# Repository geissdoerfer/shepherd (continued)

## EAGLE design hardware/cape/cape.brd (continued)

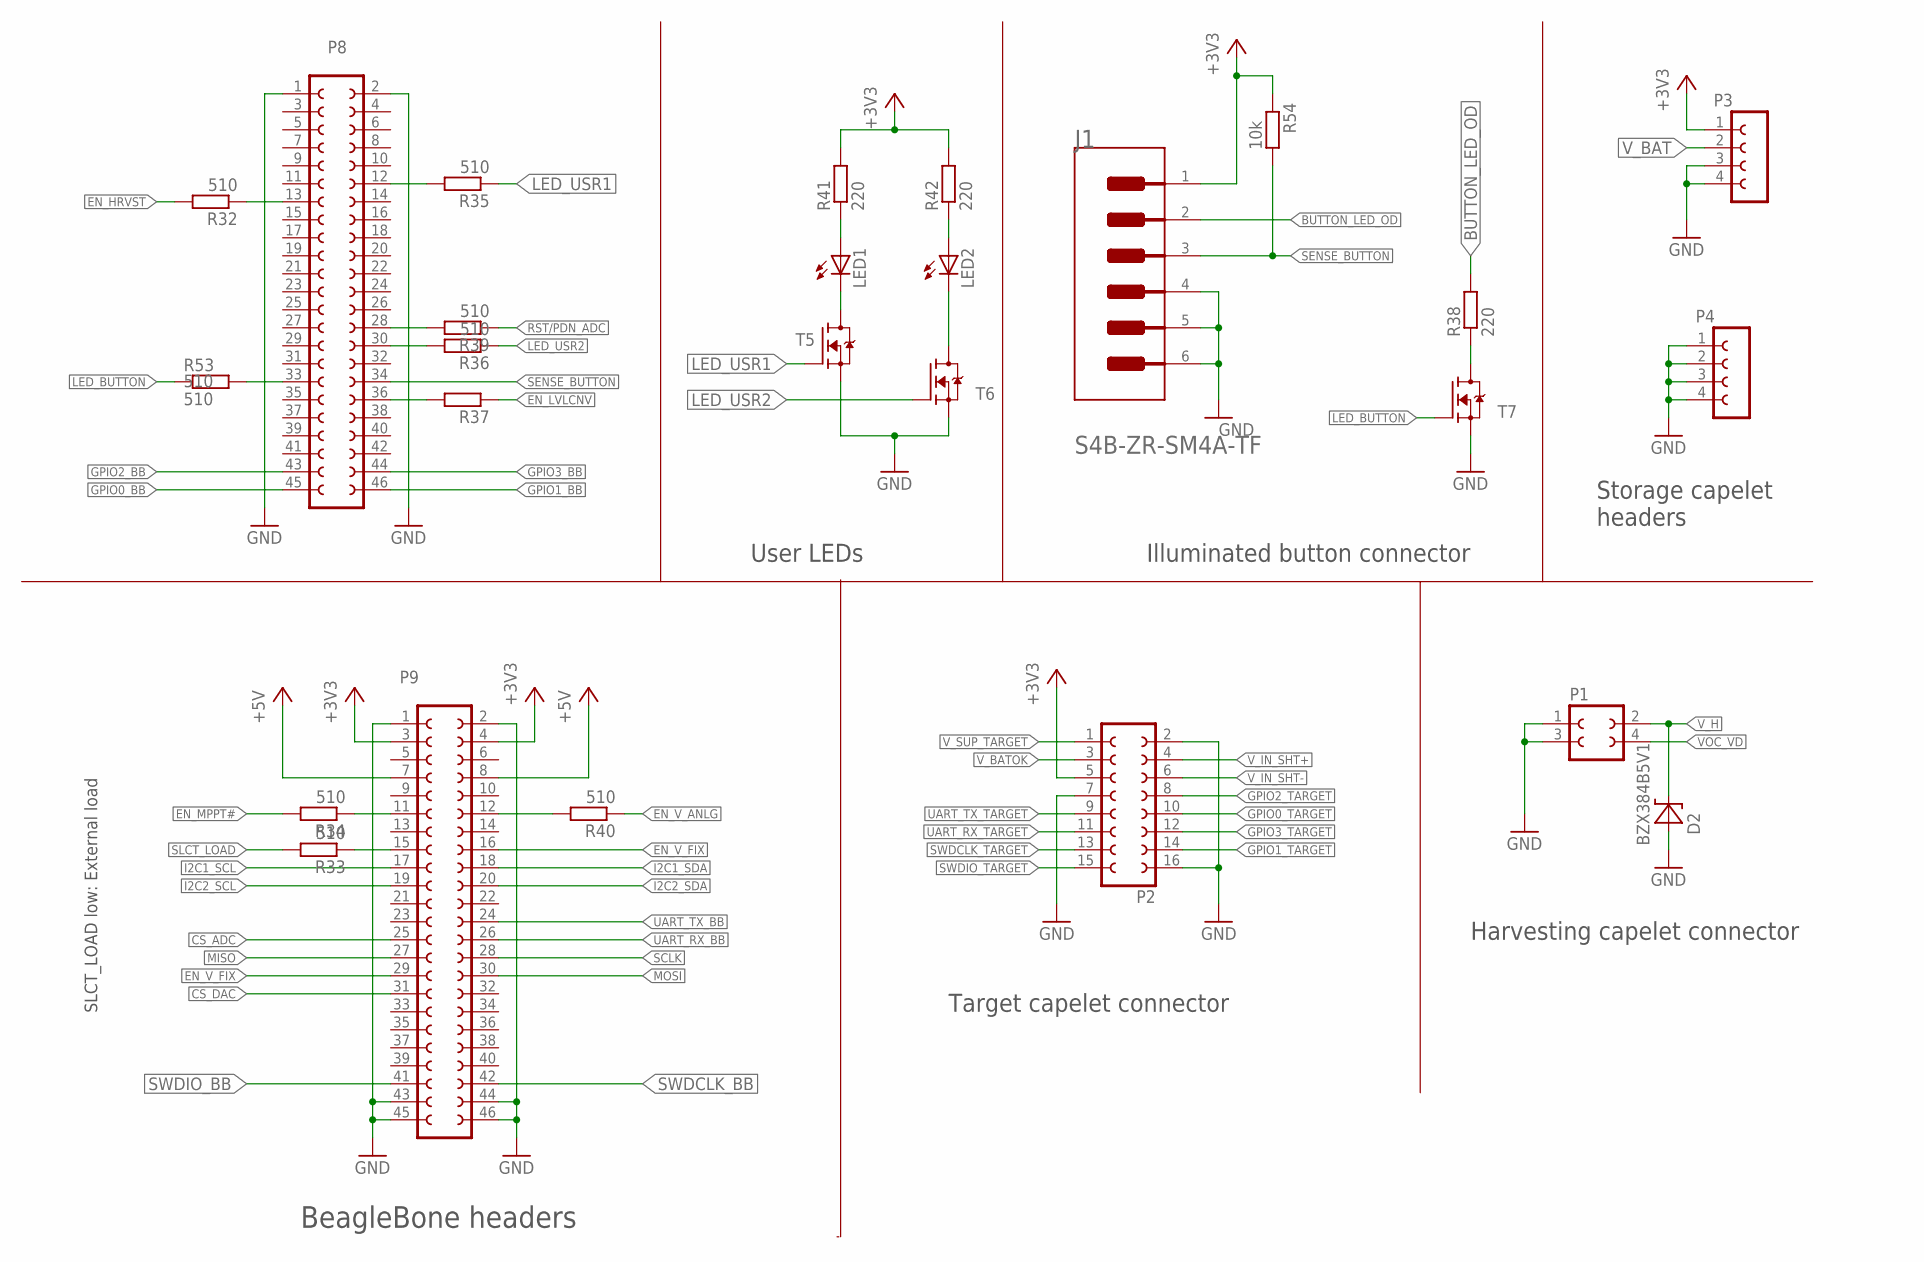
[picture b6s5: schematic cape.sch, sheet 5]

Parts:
D2: BZX384B5V1; SOD2513X110
J1: JST_S4B-ZR-SM4A-TFJST_S4B-ZR-SM4A-TF_0_0; JST_S4B-ZR-SM4A-TF_0
LED1, LED2: 598-8130-107FLED_0805; LEDC2012X75
P1: FE02-2
P2: FE08-2
P3, P4: FE04-1
P8, P9: FE23-2
R32, R33, R34, R35, R36, R37, R39, R40, R53: 510; RESC1005X40
R38, R41, R42: 220; RESC1608X55
R54: 10k; RESC1005X40
T5, T6, T7: SI2374DSSOT23-VSHAY; SOT95P237X112-3

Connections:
+3V3: J1.1, P2.5, P3.1, P9.3, P9.4, R41.2, R42.2, R54.1; also elsewhere on the board
+5V: P9.7, P9.8; also elsewhere on the board
BUTTON_LED_OD: J1.2, R38.2
CS_ADC: P9.25; also elsewhere on the board
CS_DAC: P9.31; also elsewhere on the board
EN_HRVST: R32.2; also elsewhere on the board
EN_LVLCNV: R37.1; also elsewhere on the board
EN_MPPT#: R34.2; also elsewhere on the board
EN_V_ANLG: R40.1; also elsewhere on the board
EN_V_FIX: P9.16, P9.29; also elsewhere on the board
GND: D2.2 (A), J1.4, J1.5 (MNT_1), J1.6 (MNT_2), P1.1, P1.3, P2.2, P2.7, P2.16, P3.3, P3.4, P4.1, P4.2, P4.3, P4.4, P8.1, P8.2, P9.1, P9.2, P9.43, P9.44, P9.45, P9.46, T5.2 (S), T6.2 (S), T7.2 (S); also elsewhere on the board
GPIO0_BB: P8.45; also elsewhere on the board
GPIO0_TARGET: P2.10; also elsewhere on the board
GPIO1_BB: P8.46; also elsewhere on the board
GPIO1_TARGET: P2.14; also elsewhere on the board
GPIO2_BB: P8.43; also elsewhere on the board
GPIO2_TARGET: P2.8; also elsewhere on the board
GPIO3_BB: P8.44; also elsewhere on the board
GPIO3_TARGET: P2.12; also elsewhere on the board
I2C1_SCL: P9.17; also elsewhere on the board
I2C1_SDA: P9.18; also elsewhere on the board
I2C2_SCL: P9.19; also elsewhere on the board
I2C2_SDA: P9.20; also elsewhere on the board
LED_BUTTON: R53.1, T7.1 (G)
LED_USR1: R35.1, T5.1 (G)
LED_USR2: R36.1, T6.1 (G)
MISO: P9.27; also elsewhere on the board
MOSI: P9.30; also elsewhere on the board
unnamed: LED1.1 (C), T5.3 (D)
unnamed: P8.13, R32.1
unnamed: P9.15, R33.1
unnamed: P8.28, R39.2
unnamed: P8.33, R53.2
unnamed: P8.36, R37.2
unnamed: LED1.2 (A), R41.1
unnamed: P8.12, R35.2
unnamed: LED2.1 (C), T6.3 (D)
unnamed: LED2.2 (A), R42.1
unnamed: P9.11, R34.1
unnamed: P8.30, R36.2
unnamed: R38.1, T7.3 (D)
unnamed: P9.12, R40.2
RST/PDN_ADC: R39.1; also elsewhere on the board
SCLK: P9.28; also elsewhere on the board
SENSE_BUTTON: J1.3, P8.34, R54.2
SLCT_LOAD: R33.2; also elsewhere on the board
SWDCLK_BB: P9.42; also elsewhere on the board
SWDCLK_TARGET: P2.13; also elsewhere on the board
SWDIO_BB: P9.41; also elsewhere on the board
SWDIO_TARGET: P2.15; also elsewhere on the board
UART_RX_BB: P9.26; also elsewhere on the board
UART_RX_TARGET: P2.11; also elsewhere on the board
UART_TX_BB: P9.24; also elsewhere on the board
UART_TX_TARGET: P2.9; also elsewhere on the board
VOC_VD: P1.4; also elsewhere on the board
V_BAT: P3.2; also elsewhere on the board
V_BATOK: P2.3; also elsewhere on the board
V_H: D2.1 (C), P1.2; also elsewhere on the board
V_IN_SHT+: P2.4; also elsewhere on the board
V_IN_SHT-: P2.6; also elsewhere on the board
V_SUP_TARGET: P2.1; also elsewhere on the board

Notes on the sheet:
SLCT_LOAD low: External load
Storage capelet headers
User LEDs
Harvesting capelet connector
Target capelet connector
BeagleBone headers
Illuminated button connector

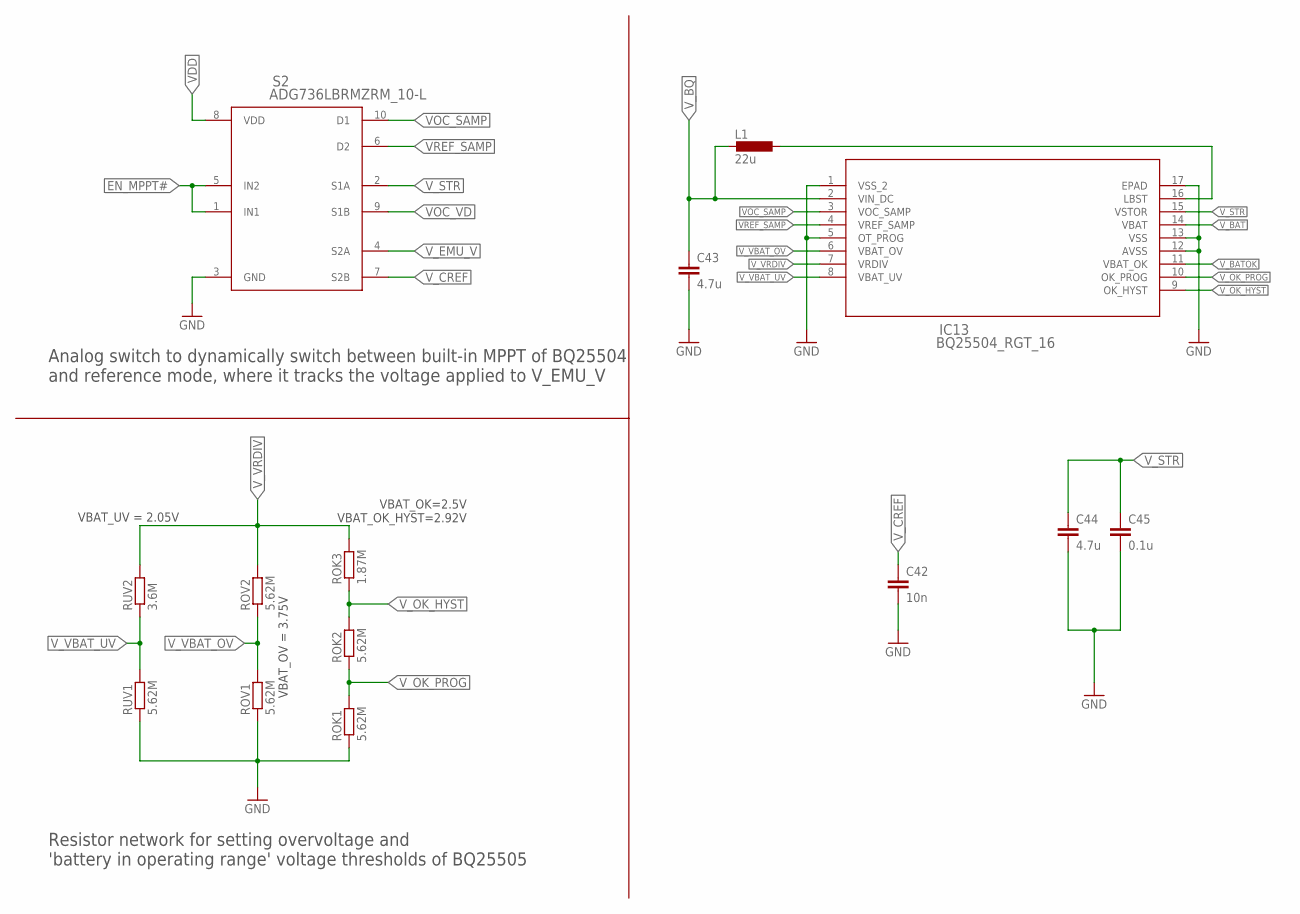
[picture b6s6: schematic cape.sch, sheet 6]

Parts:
C42: 10n; CAPC1005X55
C43, C44: 4.7u; CAPC2012X145
C45: 0.1u; CAPC1005X55
IC13: BQ25504_RGT_16; RGT16_1P7X1P7
L1: 22u; L3225P
ROK1, ROK2: 5.62M; RESC1608X55
ROK3: 1.87M; RESC1608X55
ROV1, ROV2: 5.62M; RESC1608X55
RUV1: 5.62M; RESC1608X55
RUV2: 3.6M; RESC1608X55
S2: ADG736LBRMZRM_10-L; RM_10-L

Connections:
EN_MPPT#: S2.1 (IN1), S2.5 (IN2); also elsewhere on the board
GND: C42.2, C43.2, C44.2, C45.2, IC13.1 (VSS_2), IC13.5 (OT_PROG), IC13.12 (AVSS), IC13.13 (VSS), IC13.17 (EPAD), ROK1.1, ROV1.1, RUV1.1, S2.3 (GND); also elsewhere on the board
unnamed: IC13.16 (LBST), L1.1
VDD: S2.8 (VDD); also elsewhere on the board
VOC_SAMP: IC13.3 (VOC_SAMP), S2.10 (D1)
VOC_VD: S2.9 (S1B); also elsewhere on the board
VREF_SAMP: IC13.4 (VREF_SAMP), S2.6 (D2)
V_BAT: IC13.14 (VBAT); also elsewhere on the board
V_BATOK: IC13.11 (VBAT_OK); also elsewhere on the board
V_BQ: C43.1, IC13.2 (VIN_DC), L1.2; also elsewhere on the board
V_CREF: C42.1, S2.7 (S2B)
V_EMU_V: S2.4 (S2A); also elsewhere on the board
V_OK_HYST: IC13.9 (OK_HYST), ROK2.2, ROK3.1
V_OK_PROG: IC13.10 (OK_PROG), ROK1.2, ROK2.1
V_STR: C44.1, C45.1, IC13.15 (VSTOR), S2.2 (S1A); also elsewhere on the board
V_VBAT_OV: IC13.6 (VBAT_OV), ROV1.2, ROV2.1
V_VBAT_UV: IC13.8 (VBAT_UV), RUV1.2, RUV2.1
V_VRDIV: IC13.7 (VRDIV), ROK3.2, ROV2.2, RUV2.2

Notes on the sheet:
VBAT_OK=2.5V VBAT_OK_HYST=2.92V
VBAT_OV = 3.75V
Analog switch to dynamically switch between built-in MPPT of BQ25504 and reference mode, where it tracks the voltage applied to V_EMU_V
Resistor network for setting overvoltage and 'battery in operating range' voltage thresholds of BQ25505
VBAT_UV = 2.05V

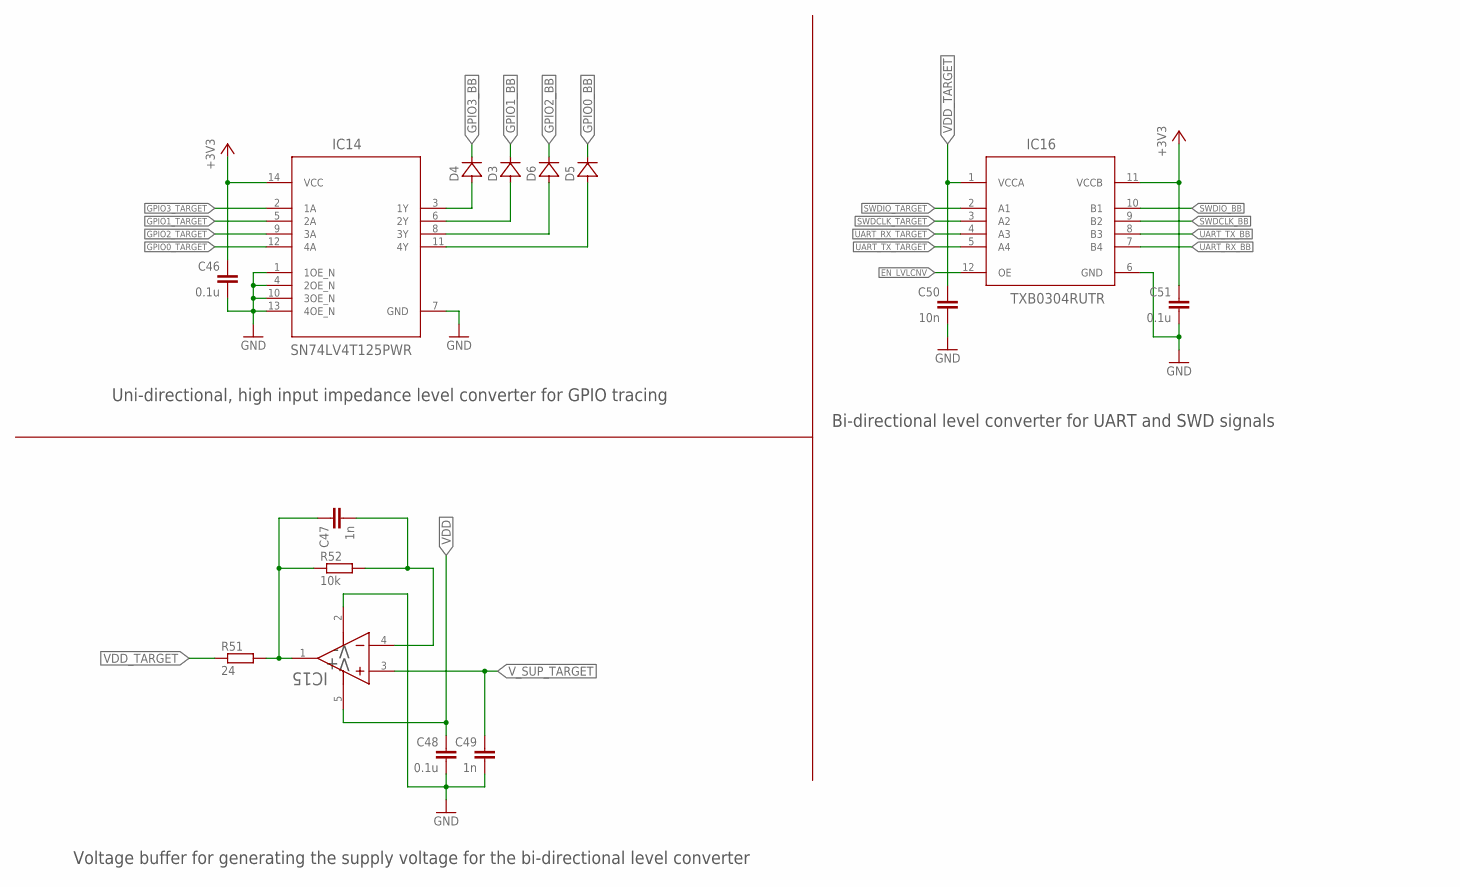
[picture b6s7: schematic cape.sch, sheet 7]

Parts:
C46, C48, C51: 0.1u; CAPC1005X55
C47, C49: 1n; CAPC1005X55
C50: 10n; CAPC1005X55
D3, D4, D5, D6: ACDBQC0130L-HF0402; DIOC1005X55N
IC14: SN74LV4T125PWR; PW0014A_N
IC15: LMP7701MF; DBV5-L
IC16: TXB0304RUTR; RUT0012A
R51: 24; RESC1005X40
R52: 10k; RESC1005X40

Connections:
+3V3: C46.1, C51.1, IC14.14 (VCC), IC16.11 (VCCB); also elsewhere on the board
EN_LVLCNV: IC16.12 (OE); also elsewhere on the board
GND: C46.2, C48.2, C49.2, C50.2, C51.2, IC14.1 (1OE_N), IC14.4 (2OE_N), IC14.7 (GND), IC14.10 (3OE_N), IC14.13 (4OE_N), IC15.2 (V-), IC16.6 (GND); also elsewhere on the board
GPIO0_BB: D5.2 (C); also elsewhere on the board
GPIO0_TARGET: IC14.12 (4A); also elsewhere on the board
GPIO1_BB: D3.2 (C); also elsewhere on the board
GPIO1_TARGET: IC14.5 (2A); also elsewhere on the board
GPIO2_BB: D6.2 (C); also elsewhere on the board
GPIO2_TARGET: IC14.9 (3A); also elsewhere on the board
GPIO3_BB: D4.2 (C); also elsewhere on the board
GPIO3_TARGET: IC14.2 (1A); also elsewhere on the board
unnamed: D4.1 (A), IC14.3 (1Y)
unnamed: C47.1, IC15.1 (OUT), R51.2, R52.1
unnamed: D3.1 (A), IC14.6 (2Y)
unnamed: D6.1 (A), IC14.8 (3Y)
unnamed: D5.1 (A), IC14.11 (4Y)
unnamed: C47.2, IC15.4 (IN-), R52.2
SWDCLK_BB: IC16.9 (B2); also elsewhere on the board
SWDCLK_TARGET: IC16.3 (A2); also elsewhere on the board
SWDIO_BB: IC16.10 (B1); also elsewhere on the board
SWDIO_TARGET: IC16.2 (A1); also elsewhere on the board
UART_RX_BB: IC16.7 (B4); also elsewhere on the board
UART_RX_TARGET: IC16.4 (A3); also elsewhere on the board
UART_TX_BB: IC16.8 (B3); also elsewhere on the board
UART_TX_TARGET: IC16.5 (A4); also elsewhere on the board
VDD: C48.1, IC15.5 (V+); also elsewhere on the board
VDD_TARGET: C50.1, IC16.1 (VCCA), R51.1
V_SUP_TARGET: C49.1, IC15.3 (IN+); also elsewhere on the board

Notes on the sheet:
Bi-directional level converter for UART and SWD signals
Uni-directional, high input impedance level converter for GPIO tracing
Voltage buffer for generating the supply voltage for the bi-directional level converter

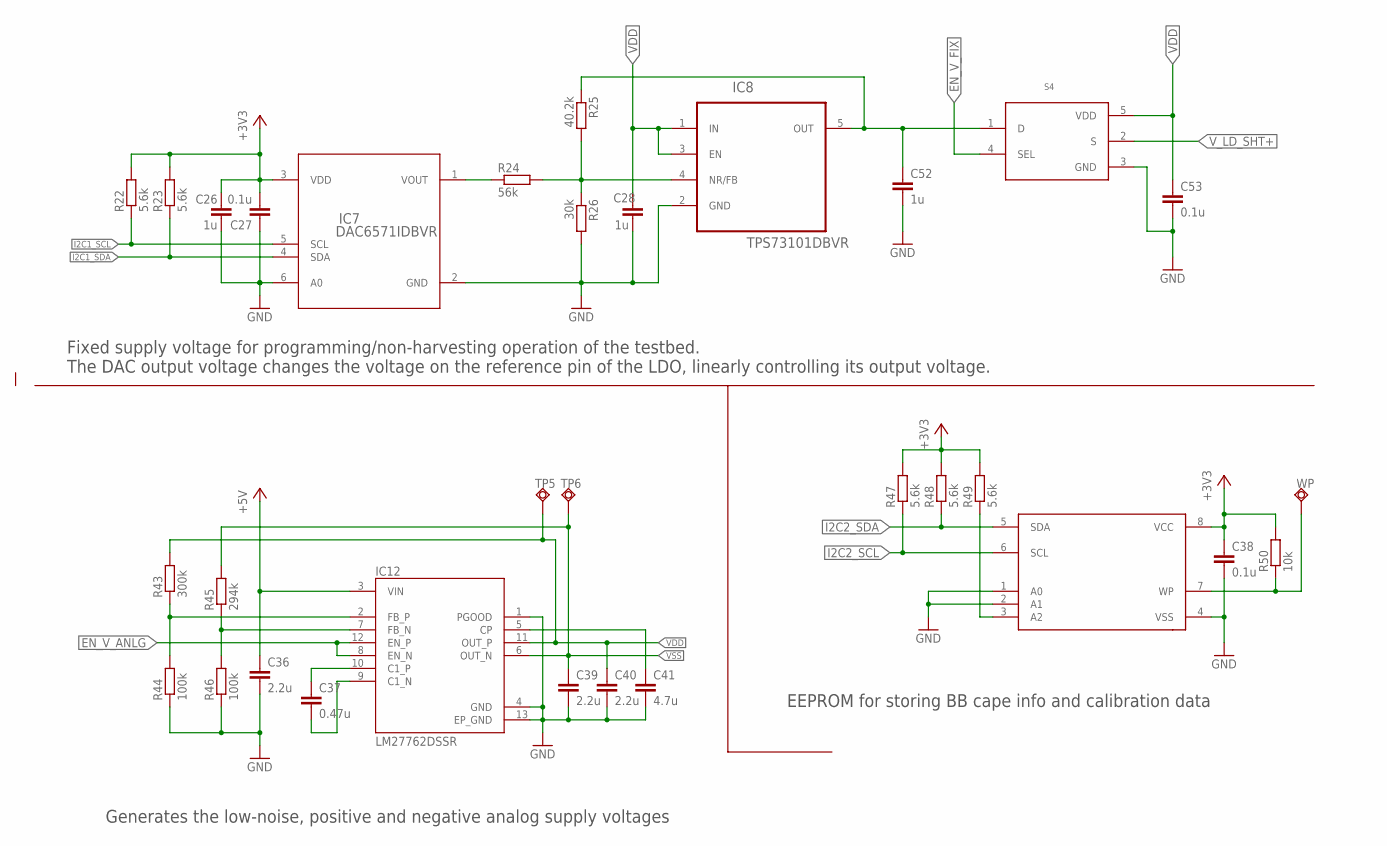
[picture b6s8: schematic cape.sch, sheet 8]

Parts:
C26, C28, C52: 1u; CAPC1608X95
C27, C38, C53: 0.1u; CAPC1005X55
C36, C39, C40: 2.2u; CAPC2012X145
C37: 0.47u; CAPC1608X95
C41: 4.7u; CAPC2012X145
IC7: DAC6571IDBVR
IC8: TPS73101DBVR; SOT95P280X145-5N
IC11: CAT24C256WI-GT3; SO08
IC12: LM27762DSSR; VREG_LM27762DSSR
R22, R23, R47, R48, R49: 5.6k; RESC1005X40
R24: 56k; RESC1005X40
R25: 40.2k; RESC1005X40
R26: 30k; RESC1005X40
R43: 300k; RESC1005X40
R44, R46: 100k; RESC1005X40
R45: 294k; RESC1005X40
R50: 10k; RESC1005X40
S4: TMUX1101DCK; DCK5
TP5, TP6: TPSQTP06R; TP06R
WP: TPSQTP06R; TP06R

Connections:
+3V3: C26.1, C27.2, C38.1, IC7.3 (VDD), IC11.8 (VCC), R22.2, R23.2, R47.2, R48.2, R49.2, R50.2; also elsewhere on the board
+5V: C36.1, IC12.3 (VIN); also elsewhere on the board
EN_V_ANLG: IC12.8 (EN_N), IC12.12 (EN_P); also elsewhere on the board
EN_V_FIX: S4.4 (SEL); also elsewhere on the board
GND: C26.2, C27.1, C28.2, C36.2, C38.2, C39.2, C40.2, C41.2, C52.2, C53.2, IC7.2 (GND), IC7.6 (A0), IC8.2 (GND), IC11.1 (A0), IC11.2 (A1), IC11.4 (VSS), IC12.1 (PGOOD), IC12.4 (GND), IC12.13 (EP_GND), R26.2, R44.1, R46.1, S4.3 (GND); also elsewhere on the board
I2C1_SCL: IC7.5 (SCL), R22.1; also elsewhere on the board
I2C1_SDA: IC7.4 (SDA), R23.1; also elsewhere on the board
I2C2_SCL: IC11.6 (SCL), R47.1; also elsewhere on the board
I2C2_SDA: IC11.5 (SDA), R48.1; also elsewhere on the board
unnamed: C52.1, IC8.5 (OUT), R25.1, S4.1 (D)
unnamed: IC8.4 (NR/FB), R24.2, R25.2, R26.1
unnamed: IC12.2 (FB_P), R43.1, R44.2
unnamed: IC7.1 (VOUT), R24.1
unnamed: IC11.7 (WP), R50.1, WP.TP
unnamed: IC12.7 (FB_N), R45.1, R46.2
unnamed: IC11.3 (A2), R49.1
unnamed: C41.1, IC12.5 (CP)
unnamed: C37.2, IC12.9 (C1_N)
unnamed: C37.1, IC12.10 (C1_P)
VDD: C28.1, C40.1, C53.1, IC8.1 (IN), IC8.3 (EN), IC12.11 (OUT_P), R43.2, S4.5 (VDD), TP5.TP; also elsewhere on the board
VSS: C39.1, IC12.6 (OUT_N), R45.2, TP6.TP; also elsewhere on the board
V_LD_SHT+: S4.2 (S); also elsewhere on the board

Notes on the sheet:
Fixed supply voltage for programming/non-harvesting operation of the testbed. The DAC output voltage changes the voltage on the reference pin of the LDO, linearly controlling its output voltage.
Generates the low-noise, positive and negative analog supply voltages
EEPROM for storing BB cape info and calibration data

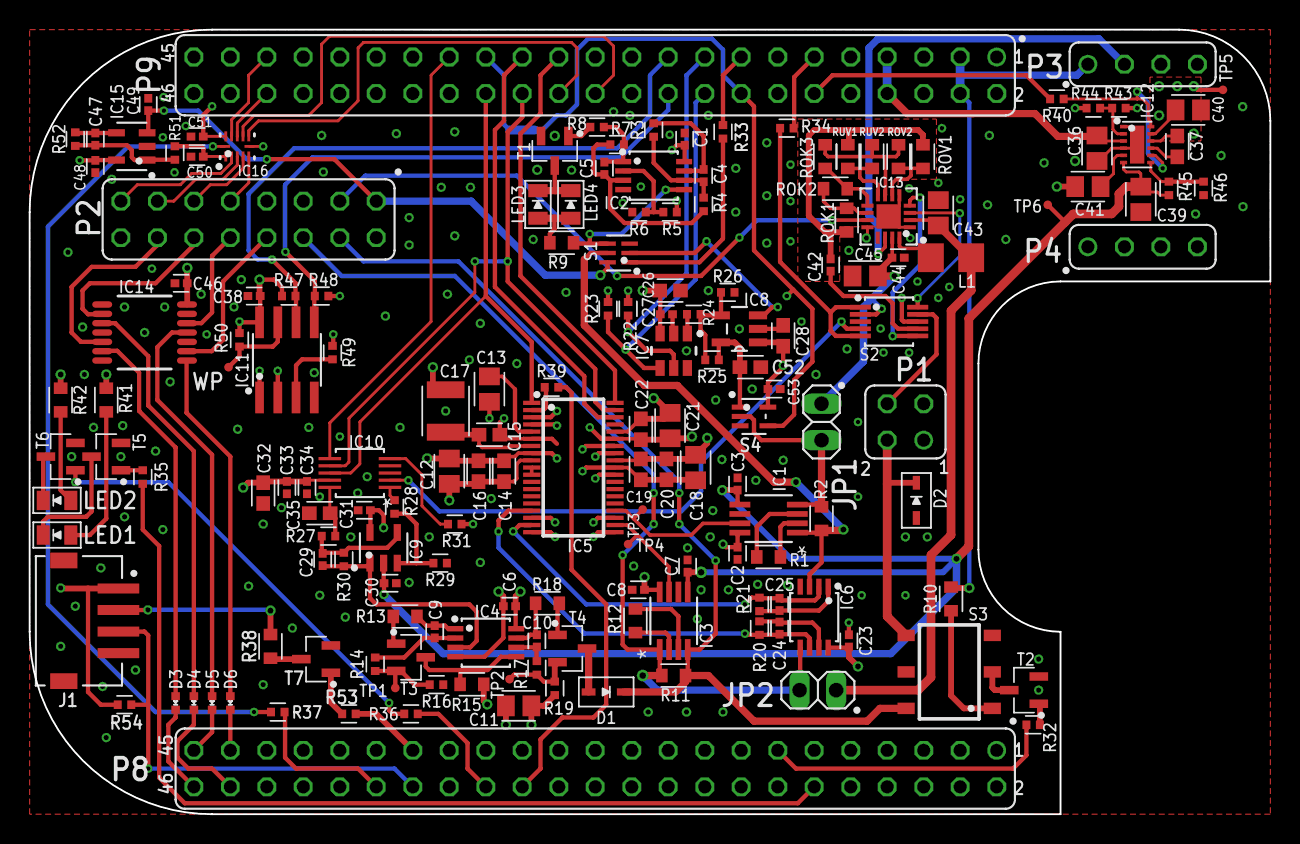
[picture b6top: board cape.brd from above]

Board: 4 copper layers, 86.4 x 54.6 mm, 171 parts (0 on the bottom side), 134 nets.

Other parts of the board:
U$1, U$2, U$3: REFMARK

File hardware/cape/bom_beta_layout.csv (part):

"BILL OF MATERIAL WITH BETA STOCK, GROUPED BY VALUES, AS OF 09.10.2015",,,,,,,,,,,,,,,,,,
Part,Value,Device,Package,Description,Description2,Qty,Place_YES/NO,Povided_by_customer_YES/NO,Distributor,Ordernumber,Weblink,Remarks_customer,Unit_price,Total_price,REMARKS_BETA,OPTION1,OPTION2,OPTION3
"C1, C2, C3, C6, C7, C8, C23, C27, C30, C31, C38, C45, C46, C48, C51",0.1u,C_SMD0402,CAPC1005X55, , ,15,YES,NO,Beta,7235228,http://de.rs-online.com/web/p/ceramic-multilayer-capacitors/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, , , , , , , 
"C4, C5, C9, C24, C25, C29, C33, C34, C47, C49",1n,C_SMD0402,CAPC1005X55, , ,10,YES,NO,Beta,147566,http://de.rs-online.com/web/p/keramik-multilayer-kondensator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, , , , , , , 
C10,2.2n,C_SMD0402,CAPC1005X55, , ,1,YES,NO,Digi-Key,399-3068-1-ND,https://www.digikey.com/products/en?keywords=399-3068-1-ND, , , , , , , 
"C11, C12, C13, C18, C21",10u,C_SMD0805,CAPC2012X145, , ,5,YES,NO,Beta,6911161P,http://uk.rs-online.com/web/search/searchBrowseAction.html?m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, , , , , , , 
"C14, C15, C16, C19, C20, C22, C26, C28, C32, C35",1u,C_SMD0603,CAPC1608X95, , ,10,YES,NO,Beta,6911142,http://de.rs-online.com/web/p/keramik-multilayer-kondensator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, , , , , , , 
C17,22u,C_SMD1210,CAPC3225X280, , ,1,YES,NO,Digi-Key,399-7451-1-ND,https://www.digikey.com/products/en?keywords=399-7451-1-ND, , , , , , , 
"C36, C39, C40",2.2u,C_SMD0805,CAPC2012X145, , ,3,YES,NO,Digi-Key,1276-2956-1-ND,https://www.digikey.com/products/en?keywords=1276-2956-1-ND, , , , , , , 
C37,0.47u,C_SMD0603,CAPC1608X95, , ,1,YES,NO,Digi-Key,399-7934-1-ND,https://www.digikey.com/products/en?keywords=399-7934-1-ND, , , , , , , 
"C41, C43, C44",4.7u,C_SMD0805,CAPC2012X145, , ,3,YES,NO,Beta,6911186P,http://uk.rs-online.com/web/search/searchBrowseAction.html?m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, , , , , , , 
"C42, C50",10n,C_SMD0402,CAPC1005X55, , ,2,YES,NO,Beta,147049,http://de.rs-online.com/web/p/keramik-multilayer-kondensator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, , , , , , , 
"D1, D2",BAT43WS-HE3SOD-323,BAT43WS-HE3SOD-323,SOD2513X110, , ,2,YES,NO,Digi-Key,BAT43WS-HE3-08GICT-ND,https://www.digikey.com/products/en?keywords=BAT43WS-HE3-08GICT-ND, , , , , , , 
D3,BZX384B5V1,BZX384B5V1,SOD2513X110, , ,1,YES,NO,Digi-Key,BZX384C5V1-HE3-08GICT-ND,https://www.digikey.com/products/en?keywords=BZX384C5V1-HE3-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, , , , , , , 
"D4, D5, D6, D7",ACDBQC0130L-HF0402,ACDBQC0130L-HF0402,DIOC0905X50N, , ,4,YES,NO,Digi-Key,641-2041-1-ND,https://www.digikey.com/products/en?keywords=641-2041-1-ND, , , , , , , 
"IC1, IC3",AD8422BRMZ,AD8422BRMZ,RM_8-L, , ,2,YES,NO,Digi-Key,AD8422ARMZ-ND,https://www.digikey.com/products/en?keywords=AD8422ARMZ-ND, , , , , , , 
"IC2, IC4, IC6",OPA2388DGK8_L,OPA2388DGK8_L,DGK8-L, , ,3,YES,NO,Digi-Key,296-50277-1-ND,https://www.digikey.com/products/en?keywords=296-50277-1-ND, , , , , , , 
IC5,ADS8694TSSOP38,ADS8694TSSOP38,TSSOP38, , ,1,YES,NO,Digi-Key,296-42531-5-ND,https://www.digikey.com/products/en?keywords=296-42531-5-ND, , , , , , , 
IC7,DAC6571IDBVR,DAC6571IDBVR,DAC6571IDBVR, , ,1,YES,NO,Digi-Key,296-48525-1-ND,https://www.digikey.com/products/en?keywords=296-48525-1-ND, , , , , , , 
IC8,TPS73101DBVR,TPS73101DBVR,SOT95P280X145-5N,"Cap-Free, NMOS, 400mA Low-Dropout Regulator with Reverse Current Protection", ,1,YES,NO,Digi-Key,296-27058-1-ND,https://www.digikey.com/products/en?keywords=296-27058-1-ND, , , , , , , 
"IC9, IC15",LMP7701MF,LMP7701MF,DBV5-L, , ,2,YES,NO,Digi-Key,LMP7701MF/NOPBCT-ND,https://www.digikey.com/products/en?keywords=LMP7701MF/NOPBCT-ND, , , , , , , 
IC10,DAC8562_DGS_10,DAC8562_DGS_10,DGS10, , ,1,YES,NO,Digi-Key,296-43693-1-ND,https://www.digikey.com/products/en?keywords=296-43693-1-ND, , , , , , , 
IC11,CAT24C256WI-GT3,CAT24C256WI-GT3,SO08, , ,1,YES,NO,Digi-Key,CAT24C256WI-GT3OSCT-ND,https://www.digikey.com/products/en?keywords=CAT24C256WI-GT3OSCT-ND, , , , , , , 
IC12,LM27762DSSR,LM27762DSSR,VREG_LM27762DSSR,Low-Noise Positive- and Negative-Output Charge Pump With Integrated LDO 12-WSON -40 to 85, ,1,YES,NO,Digi-Key,296-44944-1-ND,https://www.digikey.com/products/en?keywords=296-44944-1-ND, , , , , , , 
IC13,BQ25504_RGT_16,BQ25504_RGT_16,RGT16_1P7X1P7, , ,1,YES,NO,Digi-Key,296-29741-1-ND,https://www.digikey.com/products/en?keywords=296-29741-1-ND, , , , , , , 
IC14,SN74LV4T125PWR,SN74LV4T125PWR,PW0014A_N, , ,1,YES,NO,Digi-Key,296-40545-1-ND,https://www.digikey.com/products/en?keywords=296-40545-1-ND, , , , , , , 
IC16,TXB0304RUTR,TXB0304RUTR,RUT0012A, , ,1,YES,NO,Digi-Key,296-29682-1-ND,https://www.digikey.com/products/en?keywords=296-29682-1-ND, , , , , , , 
"JP1, JP2", ,PINHD-1X2,1X02,PIN HEADER, ,2,YES,NO,Digi-Key,732-5315-ND,https://www.digikey.com/products/en?keywords=732-5315-ND, , , , , , , 
K1,G3VM-31HR22SOP,G3VM-31HR22SOP,SOP06,PhotoMOS Relay NAiS, ,1,YES,NO,Digi-Key,Z8598-ND,https://www.digikey.com/products/en?keywords=Z8598-ND, , , , , , , 
L1,22u,L-EUL3225P,L3225P,"INDUCTOR, European symbol", ,1,YES,NO,Digi-Key,732-7315-1-ND,https://www.digikey.com/products/en?keywords=732-7315-1-ND, , , , , , , 
"LED1, LED2, LED3, LED4",598-8130-107FLED_0805,598-8130-107FLED_0805,LEDC2012X75, , ,4,YES,NO,Digi-Key,350-2040-1-ND,https://www.digikey.com/products/en?keywords=350-2040-1-ND, , , , , , , 
P1, ,FE02-2,FE02-2,FEMALE HEADER, ,1,YES,NO,Digi-Key,SAM1212-02-ND,https://www.digikey.com/products/en?keywords=SAM1212-02-ND, , , , , , , 
P2, ,FE08-2,FE08-2,FEMALE HEADER, ,1,YES,NO,Digi-Key,SAM1212-08-ND,https://www.digikey.com/products/en?keywords=SAM1212-08-ND, , , , , , , 
"P3, P4", ,FE04-1,FE04-1,FEMALE HEADER, ,2,YES,NO,Digi-Key,SAM1213-04-ND,https://www.digikey.com/products/en?keywords=SAM1213-04-ND, , , , , , , 
"P8, P9", ,FE23-2,FE23-2,FEMALE HEADER, ,2,YES,NO,Digi-Key,SAM1204-23-ND ,https://www.digikey.com/products/en?keywords=SAM1204-23-ND, , , , , , , 
"R1, R12, R15",402,R_SMD0603,RESC1608X55, , ,3,YES,NO,Digi-Key,P19926CT-ND,https://www.digikey.com/products/en?keywords=P19926CT-ND, , , , , , , 
"R2, R11",2,R_SMD0603,RESC1608X55, , ,2,YES,NO,Digi-Key,A102258CT-ND,https://www.digikey.com/products/en?keywords=A102258CT-ND, , , , , , , 
"R3, R20, R21, R51",24,R_SMD0402,RESC1005X40, , ,4,YES,NO,Digi-Key,YAG3073CT-ND,https://www.digikey.com/products/en?keywords=YAG3073CT-ND, , , , , , , 
R4,2.4k,R_SMD0402,RESC1005X40, , ,1,YES,NO,Digi-Key,311-2.40KLRCT-ND,https://www.digikey.com/products/en?keywords=311-2.40KLRCT-ND, , , , , , , 
R5,3.6k,R_SMD0402,RESC1005X40, , ,1,YES,NO,Digi-Key,311-3.6KLRCT-ND,https://www.digikey.com/products/en?keywords=311-3.6KLRCT-ND, , , , , , , 
"R6, R7, R14, R17, R31, R50, R52",10k,R_SMD0402,RESC1005X40, , ,7,YES,NO,Beta,618-5832,http://de.rs-online.com/web/p/products/6185832/?searchTerm=6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, , , , , , , 
"R8, R16, R28, R30",1.2k,R_SMD0402,RESC1005X40, , ,4,YES,NO,Beta,618-6138,http://de.rs-online.com/web/p/products/6186138/?searchTerm=6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, , , , , , , 
R9,91,R_SMD0603,RESC1608X55, , ,1,YES,NO,Digi-Key,311-91.0HRCT-ND,https://www.digikey.com/products/en?keywords=311-91.0HRCT-ND, , , , , , , 
"R10, R13, R18, R41, R42",220,R_SMD0603,RESC1608X55, , ,5,YES,NO,Beta,6979191,http://uk.rs-online.com/web/search/searchBrowseAction.html?m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, , , , , , , 
R19,30,R_SMD0402,RESC1005X40, , ,1,YES,NO,Digi-Key,A102788CT-ND,https://www.digikey.com/products/en?keywords=A102788CT-ND, , , , , , , 
"R22, R23, R47, R48, R49",5.6k,R_SMD0402,RESC1005X40, , ,5,YES,NO,Beta,698-0693,http://de.rs-online.com/web/p/products/6980693/?searchTerm=6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, , , , , , , 
R24,56k,R_SMD0402,RESC1005X40, , ,1,YES,NO,Beta,698-6761,http://de.rs-online.com/web/p/products/6986761/?searchTerm=6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, , , , , , , 
R25,40.2k,R_SMD0402,RESC1005X40, , ,1,YES,NO,Digi-Key,311-40.2KLRCT-ND,https://www.digikey.com/products/en?keywords=311-40.2KLRCT-ND, , , , , , , 
R26,30k,R_SMD0402,RESC1005X40, , ,1,YES,NO,Digi-Key,311-30.0KLRCT-ND,https://www.digikey.com/products/en?keywords=311-30.0KLRCT-ND, , , , , , , 
"R27, R29, R44, R46",100k,R_SMD0402,RESC1005X40, , ,4,YES,NO,Beta,6986783,http://uk.rs-online.com/web/search/searchBrowseAction.html?m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, , , , , , , 
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
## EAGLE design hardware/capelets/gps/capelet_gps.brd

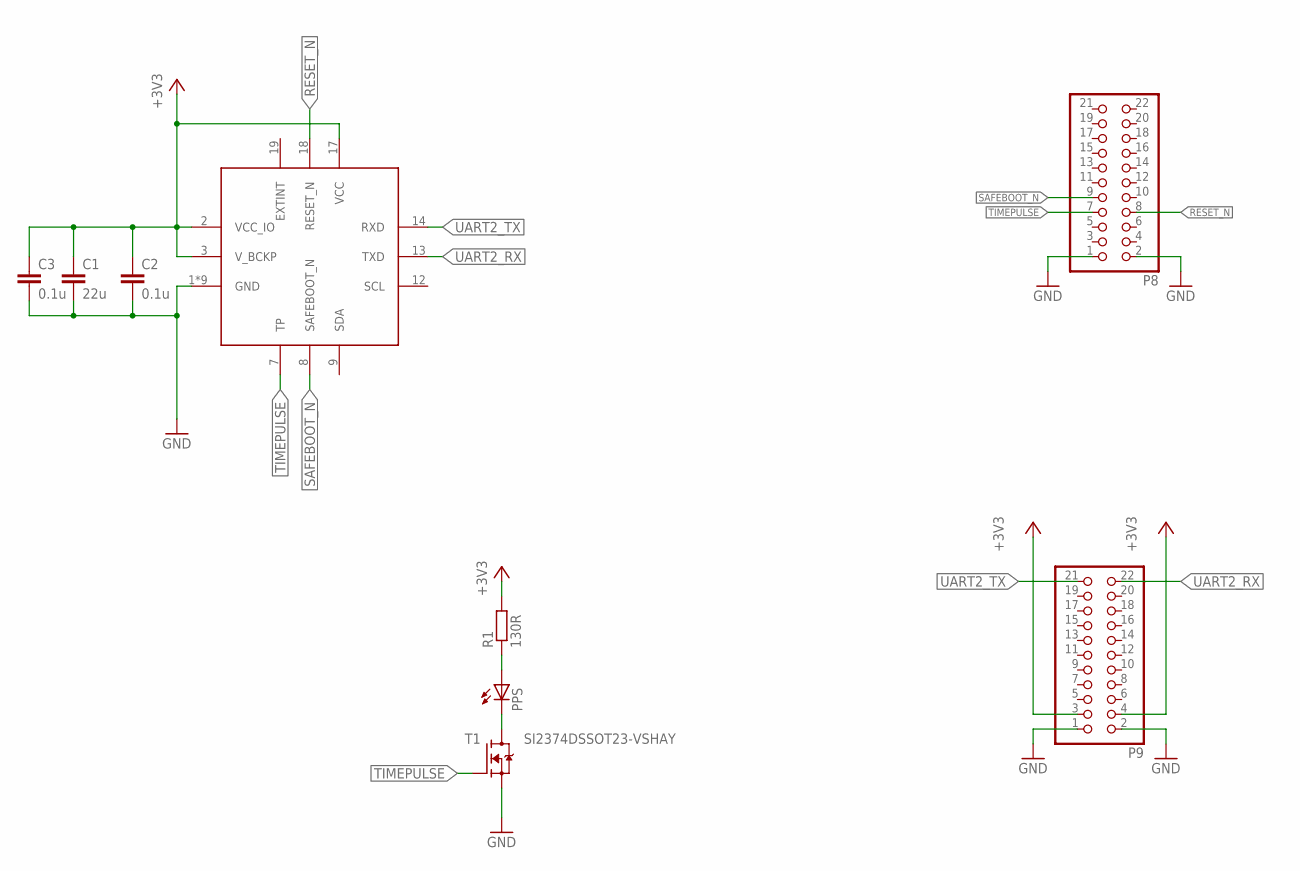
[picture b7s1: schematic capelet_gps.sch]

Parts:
C1: 22u; CAPC3225X280
C2, C3: 0.1u; CAPC2012X145
IC1: SAM-M8Q
P8, P9: PINHD-2X11; 2X11
PPS: 598-8130-107FLED_0805; LEDC2012X75
R1: 130R; RESC2012X65
T1: SI2374DSSOT23-VSHAY; SOT95P237X112-3

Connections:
+3V3: C1.1, C2.1, C3.1, IC1.2 (VCC_IO), IC1.3 (V_BCKP), IC1.17 (VCC), P9.3 (4), P9.4 (3), R1.2
GND: C1.2, C2.2, C3.2, IC1.1 (GND), IC1.4 (GND), IC1.5 (GND), IC1.6 (GND), IC1.10 (GND), IC1.11 (GND), IC1.15 (GND), IC1.16 (GND), IC1.20 (GND), P8.1 (2), P8.2 (1), P9.1 (2), P9.2 (1), T1.2 (S)
unnamed: PPS.1 (C), T1.3 (D)
unnamed: PPS.2 (A), R1.1
RESET_N: IC1.18 (RESET_N), P8.8 (7)
SAFEBOOT_N: IC1.8 (SAFEBOOT_N), P8.9 (10)
TIMEPULSE: IC1.7 (TP), P8.7 (8), T1.1 (G)
UART2_RX: IC1.13 (TXD), P9.22 (21)
UART2_TX: IC1.14 (RXD), P9.21 (22)

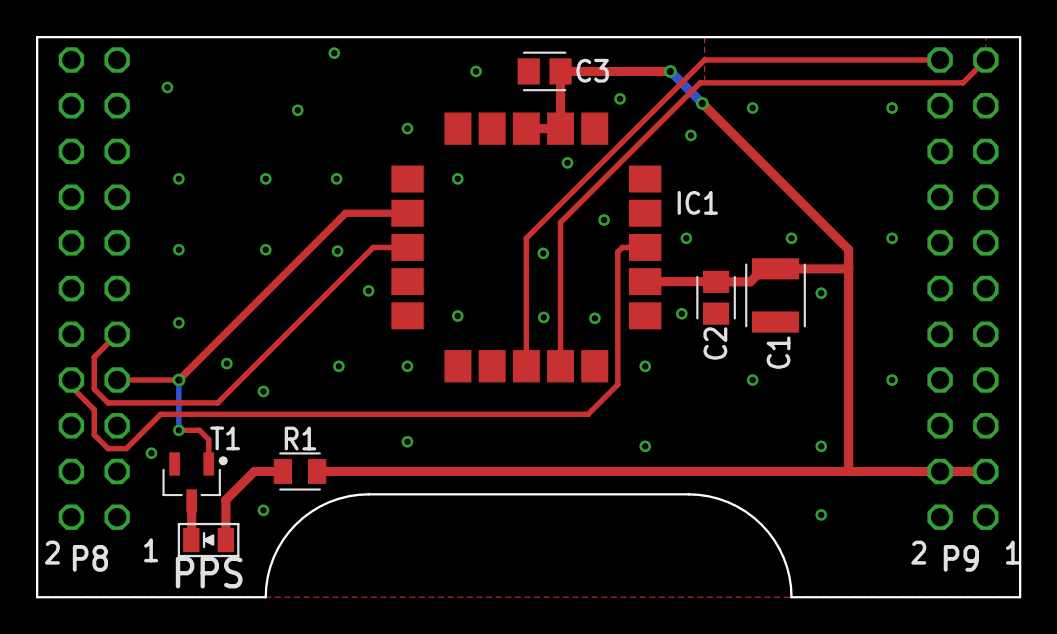
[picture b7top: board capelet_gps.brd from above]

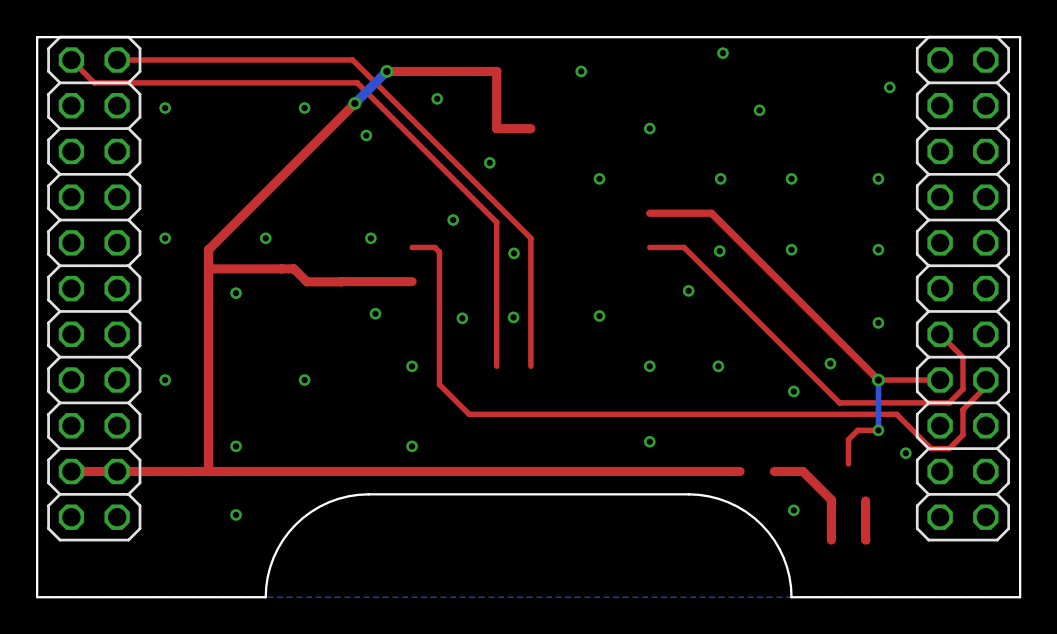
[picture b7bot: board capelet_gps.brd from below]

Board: 2 copper layers, 54.6 x 31.1 mm, 13 parts (2 on the bottom side), 9 nets.

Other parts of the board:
U$1, U$2, U$4: REFMARK
U$3: SHPRD_CPLT_G

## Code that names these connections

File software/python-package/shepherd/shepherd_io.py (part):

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        """
        state_str = "enabled" if state else "disabled"
        logger.debug(f"Set power-supplies of shepherd-cape to {state_str}")
        self.gpios["en_v_anlg"].write(state)

    def set_mppt(self, state: bool) -> NoReturn:
        """Enables or disables Maximum Power Point Tracking of BQ25505
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        """
        state_str = "enabled" if state else "disabled"
        logger.debug(f"Set MPPT-state of BW25505 to {state_str}")
        self.gpios["en_mppt"].write(not state)

    def set_harvester(self, state: bool) -> NoReturn:
        """Enables or disables connection to the harvester.
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        """
        state_str = "enabled" if state else "disabled"
        logger.debug(f"Connection to Harvester is {state_str}")
        self.gpios["en_hrvst"].write(state)

    def set_ldo_voltage(self, voltage: float) -> NoReturn:
        """Enables or disables the constant voltage regulator.
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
